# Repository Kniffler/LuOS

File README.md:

# LµOS
Loser µ-controller Operating System

A neat little contraption of my own design.

# TODO
- Add setting functionality
- Add comments and revise code in `splitter.c` and `lcdspi.h`
- Add functionality to flash (this is a bootloader afterall)
- Continue the GSM General Settings Manager library to add file support

## Contents:
- [The Bootloader](#bootloader)
- [The settings file structure](#the-settings-file-structure)
- [Build guide](#build-guide)
	- [Getting and building the project](#getting-and-building-the-project)
- [Changes and Libraries](#changes-and-libraries)
- [TODO](#todo)

# The Bootloader
Upon launching the picocalc the bootloader will be the first thing you interface with, every time. Much like the picocalc comes out of the box. However this bootloader also comes equipped with a custom font and interface (more on that later) as well as a settings menu. This settings menu is/will be able to access a configuration file structure on the SD card such that other apps may access it.

# The settings file structure
The menu of the bootloader is split up into 2, using the `splitter.h` interface and as such cannot go deeper than 1 folder into the file-system of the SD card. This behaviour is intentional, as it allows for a bit of organization while also keeping the ability to hide files from the user - such as the setting files.

# Build guide
This build guide assumes you are using the linux operating system where it is much easier to install the required tools and other project dependencies. 

Please consult the internet for instructions on how to get the following depedencies when compiling this project:
- The [pico sdk](https://github.com/raspberrypi/pico-sdk) for hardware support
- [CMake](https://cmake.org/download/) to guide compiling
- [git](https://github.com/git-guides) for ease of installing

> [!WARNING]
> The links provided above do not cover everything that needs to be done in order to get this project working on windows. Manual intervention may be required.

A text editor of your choice also doesn't hurt.

## Getting and building the project
Assuming you met the dependencies earlier, you can now clone this repository locally using
```
git clone https://github.com/Kniffler/LuOS
```
or 
```
gh repo clone Kniffler/LuOS
```
if you have [github cli](https://cli.github.com/) installed.

Now `cd` into the directory and finally run the build command. The build command is a little different depending on whether you have a raspberry pi pico h, pico w, pico 2h, or pico 2w.
Here are the commands for each:

pico h:
```
cmake -B build
make -C build
```

pico w:
```
cmake -B build -DPICO_BOARD=pico_w
make -C build
```

pico 2/2w:
```
cmake -B build -DPICO_BOARD=pico2
make -C build
```
The resultant uf2 file can now be found under /path/of/repository/LuOS/build/LuOS.uf2

> [!IMPORTANT]
> The `build.sh` script is not to be used if you want to run this project as is. If you plan on modifying the source code then this script is at your disposal for quick debugging, however you will need to change the DEVICE_MOUNTS_BY_NAME variable in the script if your pico mounts under a different label.

# Changes and libraries

In terms of libraries and resources of others, I have:
- Included the `lcdspi` and `i2ckbd` folders/libraries from the [official PicoCalc repository](https://github.com/clockworkpi/PicoCalc) keeping [uthash](https://github.com/troydhanson/uthash) as a submodule.
- Added the [pico-vfs](https://github.com/oyama/pico-vfs) repository as a submodule.
- Used [Picocalc_SD_Boot](https://github.com/adwuard/Picocalc_SD_Boot) for most (well, all) of the booloader code.

There is also [this article](https://github.com/adwuard/Picocalc_SD_Boot) which is linked in the Picocalc_SD_Boot repository source code. It goes into detail about the boot routine of the pico and paints a great picture of how the bootloader code works. I highly recommend checking it out.

`lcdspi` has been heavily modified to work with so called regions. Every app now needs to define one or more regions of the screen via the `lcd_region_create` function. This has also made the library considerably harder to read. In the future, comments will be added and the code will be revised in order to combat this issue.

Further explanations for regions may or may not be added to the README and a wiki (if I ever get around to making a wiki that is)

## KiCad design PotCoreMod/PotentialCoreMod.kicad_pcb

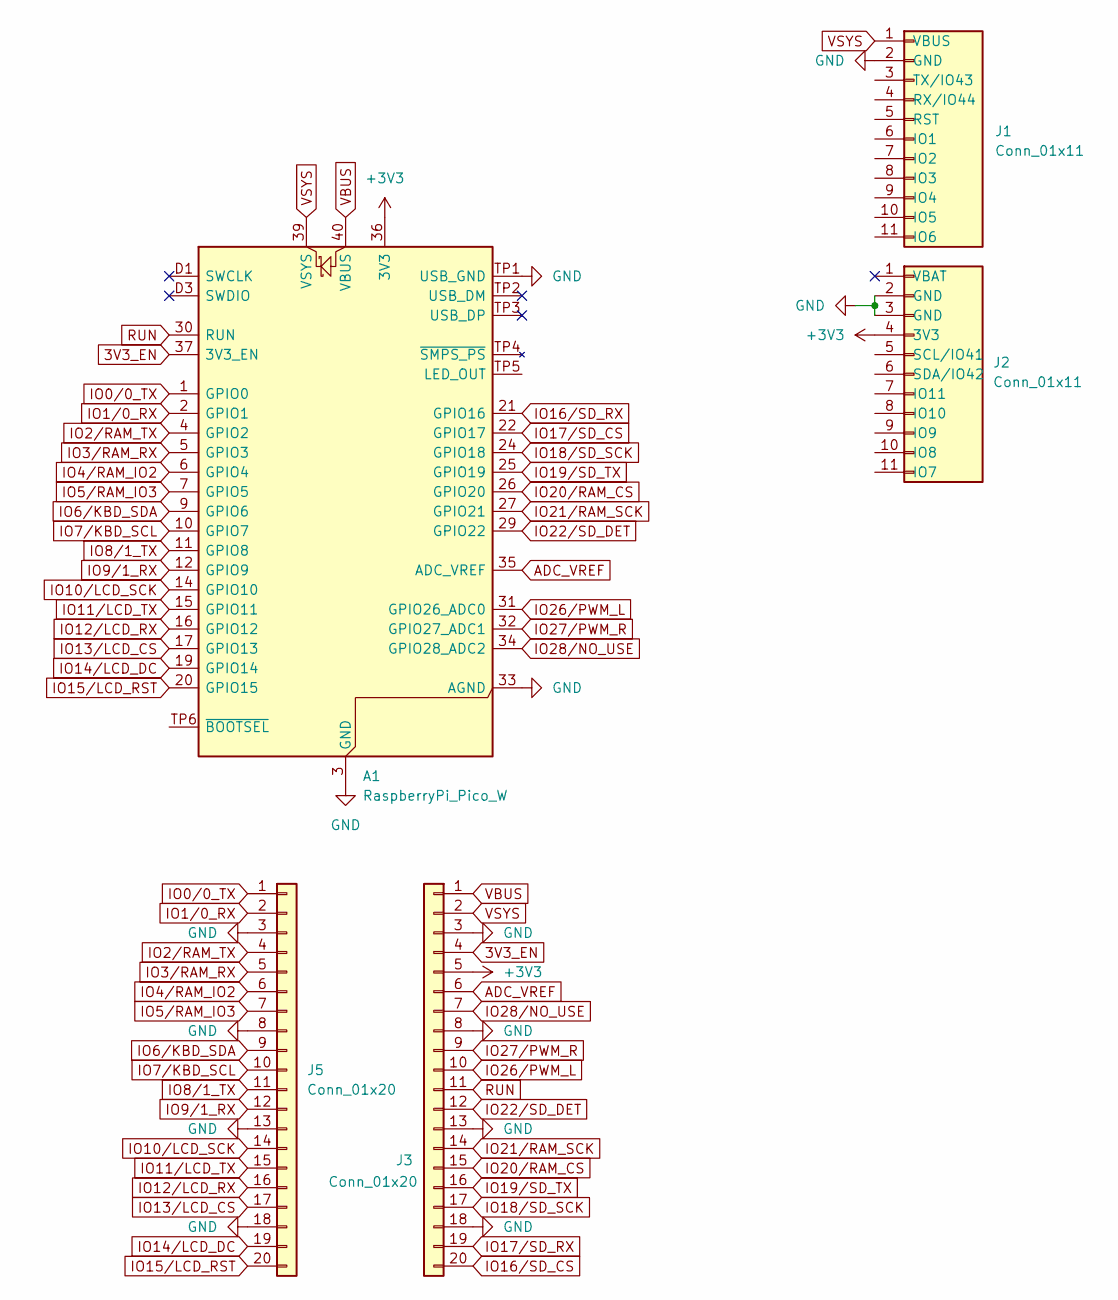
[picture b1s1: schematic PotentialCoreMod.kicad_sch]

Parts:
A1: RaspberryPi_Pico_W; RaspberryPi_Pico_W_SMD
J1, J2: Conn_01x11; PinSocket_1x11_P2.54mm_Vertical
J3, J5: Conn_01x20; PinSocket_1x20_P2.54mm_Vertical

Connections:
3V3_EN: A1.37 (3V3_EN), J3.4
+3V3: A1.36 (3V3), J2.4 (3V3), J3.5
ADC_VREF: A1.35 (ADC_VREF), J3.6
GND: A1.3 (GND), A1.8 (GND), A1.13 (GND), A1.18 (GND), A1.23 (GND), A1.28 (GND), A1.33 (AGND), A1.38 (GND), A1.D2 (GND), A1.TP1 (USB_GND), J1.2 (GND), J2.2 (GND), J2.3 (GND), J3.3, J3.8, J3.13, J3.18, J5.3, J5.8, J5.13, J5.18
IO0/0_TX: A1.1 (GPIO0), J5.1
IO1/0_RX: A1.2 (GPIO1), J5.2
IO2/RAM_TX: A1.4 (GPIO2), J5.4
IO3/RAM_RX: A1.5 (GPIO3), J5.5
IO4/RAM_IO2: A1.6 (GPIO4), J5.6
IO5/RAM_IO3: A1.7 (GPIO5), J5.7
IO6/KBD_SDA: A1.9 (GPIO6), J5.9
IO7/KBD_SCL: A1.10 (GPIO7), J5.10
IO8/1_TX: A1.11 (GPIO8), J5.11
IO9/1_RX: A1.12 (GPIO9), J5.12
IO10/LCD_SCK: A1.14 (GPIO10), J5.14
IO11/LCD_TX: A1.15 (GPIO11), J5.15
IO12/LCD_RX: A1.16 (GPIO12), J5.16
IO13/LCD_CS: A1.17 (GPIO13), J5.17
IO14/LCD_DC: A1.19 (GPIO14), J5.19
IO15/LCD_RST: A1.20 (GPIO15), J5.20
IO16/SD_CS: J3.20
IO16/SD_RX: A1.21 (GPIO16)
IO17/SD_CS: A1.22 (GPIO17)
IO17/SD_RX: J3.19
IO18/SD_SCK: A1.24 (GPIO18), J3.17
IO19/SD_TX: A1.25 (GPIO19), J3.16
IO20/RAM_CS: A1.26 (GPIO20), J3.15
IO21/RAM_SCK: A1.27 (GPIO21), J3.14
IO22/SD_DET: A1.29 (GPIO22), J3.12
IO26/PWM_L: A1.31 (GPIO26_ADC0), J3.10
IO27/PWM_R: A1.32 (GPIO27_ADC1), J3.9
IO28/NO_USE: A1.34 (GPIO28_ADC2), J3.7
RUN: A1.30 (RUN), J3.11
VBUS: A1.40 (VBUS), J3.1
VSYS: A1.39 (VSYS), J1.1 (VBUS), J3.2

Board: 2 copper layers, 5 parts (0 on the bottom side), 31 nets, no tracks yet.

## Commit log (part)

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2025-11-02 modified: .gitignore new file: .gitmodules modified: README.md
2025-11-02 new file: CMakeLists.txt new file: i2ckbd/CMakeLists.txt new file: i2ckbd/i2ckbd.c new file: i2ckbd/i2ckbd.h new file: keyboard_define.h new file: lcdspi/CMakeLists.txt new file: lcdspi/fonts/font1.h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
2025-11-14 modified: .gitmodules modified: CMakeLists.txt modified: FreeRTOS new file: FreeRTOS-Kernel modified: main.c FreeRTOS_Kernel_import.cmake include/
2025-11-14 modified: .gitmodules deleted: FreeRTOS-Kernel FreeRTOS_Kernel_import.cmake include/
2025-11-14 new file: FreeRTOS_Kernel_import.cmake new file: include/FreeRTOSConfig.h
2025-11-14 modified: README.md
2025-11-15 modified: .gitmodules modified: CMakeLists.txt modified: README.md modified: i2ckbd/i2ckbd.c modified: lcdspi/CMakeLists.txt modified: lcdspi/lcdspi.c modified: lcdspi/lcdspi.h modified: main.c new f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
2025-11-16 modified: CMakeLists.txt modified: README.md renamed: manager/CMakeLists.txt -> apps/CMakeLists.txt new file: apps/app_list.h new file: apps/fileX/main.c modified: i2ckbd/CMakeLists.txt modified: lcd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
    A lil overhaul :>
2025-11-17 modified: lcdspi/lcdspi.c modified: lcdspi/lcdspi.h modified: main.c
2025-11-22 modified: lcdspi/lcdspi.c modified: main.c
    UI cleanup
2025-11-29 modified: apps/app_list.h modified: main.c
2025-11-29 modified: main.c
2025-12-01 modified: CMakeLists.txt modified: apps/app_list.h new file: director/CMakeLists.txt new file: director/director.c new file: director/director.h modified: i2ckbd/i2ckbd.h modified: lcdspi/lcdspi.c mo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
    Moved directive implementation into separate library and switched the utility of the .test directive to receive a UART connection over GPIO 4 and 5
2025-12-02 Atualizar o README.md
2025-12-06 modified: .gitmodules modified: CMakeLists.txt modified: README.md modified: apps/CMakeLists.txt deleted: apps/app_list.h renamed: apps/fileX/main.c -> apps/filos/filos.c new file: apps/iowiz/CMakeLi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
    Massive changes in the lcdspi library
2026-02-18 modified: .gitignore modified: .gitmodules renamed: uthash -> AppShell/lcdspi/uthash modified: CMakeLists.txt deleted: FreeRTOS deleted: FreeRTOS_Kernel_import.cmake deleted: apps/CMakeLists.txt dele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
2026-02-18 new file: AppShell/CMakeLists.txt new file: AppShell/FreeRTOS/.git-blame-ignore-revs new file: AppShell/FreeRTOS/.gitattributes new file: AppShell/FreeRTOS/.github/.cSpellWords.txt new file: AppShell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
2026-02-18 deleted: AppShell/FreeRTOS/.git-blame-ignore-revs deleted: AppShell/FreeRTOS/.gitattributes deleted: AppShell/FreeRTOS/.github/.cSpellWords.txt deleted: AppShell/FreeRTOS/.github/CODEOWNERS deleted: 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
2026-02-21 modified: .gitmodules new file: AppShell/lcdspi/fonts/LuOS_System_Font.bmp new file: AppShell/lcdspi/fonts/LuOS_System_Font.h new file: AppShell/lcdspi/fonts/big endian test.bmp new file: AppShell/lc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
2026-02-21 new file: config.h
2026-03-21 Visual updates
    Splitter lib added,
    revised and added a few lcdspi functions.
    Build.sh added for convenience while programming.
2026-03-21 General things
    General things
2026-03-22 Renamed folder
    Did you not read the title?
2026-03-23 Renamed folder in add_subdirectory
2026-03-23 Updated paths
2026-03-23 Trying to fix git
    God help me
2026-03-23 idek bro
2026-03-23 Littlefs
2026-03-23 Finally, modules be fixy
2026-04-11 Settings compatability update, incomplete
    - Added GSM (General Settings Manager) library.
    - Added DEAL (Dynamic Entry Allocator)
    - An interface to store and recall entries dynamically in memory using a linked list.
    - Expanded splitter.h functionality
    - Tweaks to lcdspi and main
    - build.sh monitoring revised (still faulty)
2026-04-11 Other file changes
    Hehe
2026-04-12 Added a few functions to LISTS.h
    Don't read that much into it, I am just lazy rn.
    I'll overhaul these files at some point, for a more stable structure.
2026-04-17 Minor changes
2026-04-18 Expanded splitter library
    Changelog:
    - Added functions for customizability in the splitter.h and splitter.c
    files
    - Fixed bugs in DEAL.h, though some are surely still lurking
    - updated main.c to use filesystem as a base for the splitter interface
    - Fixed various annoyances in the UI
2026-04-19 Extenstions to splitter library
    Changelog:
    - Rewrote a lot of stuff to get rid of UI bugs
    - Added proper path tracking to splitter
    There still might be a few cases I have not tested
    TODO:
    - Find out what causes the extra character in sub folder names
2026-04-22 I am so proud of this one
    Changelog:
    - Added debug functionality over USB via a debug.h file and changes to the build.sh file
    - A lot of bug hunting in splitter.c has resulted in better (still funky) functionality
    - Good night
2026-04-23 General upgrades and fixes
    Changelog:
    - Fixed a bunch of graphical bugs in the splitter library and added path tracking
    - Started working on flashing selected file (currently non-functional)
    - Added memory map for apps
    - Added basic testing app
    - Revised the way strings are printed in the core1 wrapper for lcdspi
